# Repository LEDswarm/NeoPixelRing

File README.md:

# A custom NeoPixel ring for LEDswarm controllers

This repository contains the 3D model, schematic and PCB design of the circular NeoPixel boards designed for use with the LEDswarm controller enclosure. The design is inspired by NeoPixel Jewels, except this a special daughter board designed to mate with controller mainboards within [the 3D-printed enclosure](https://github.com/LEDswarm/enclosure).

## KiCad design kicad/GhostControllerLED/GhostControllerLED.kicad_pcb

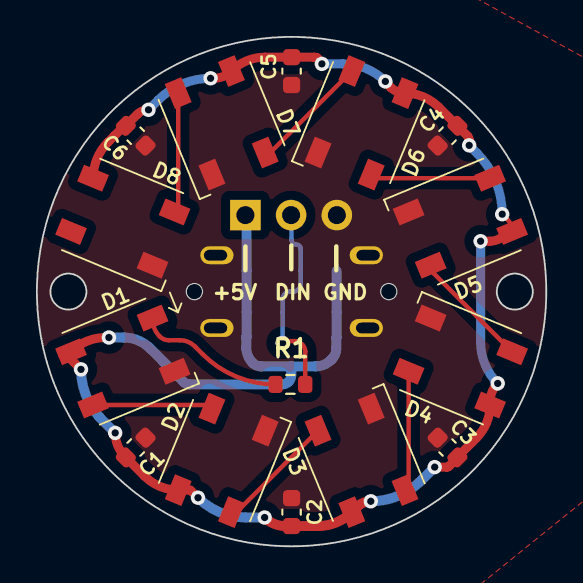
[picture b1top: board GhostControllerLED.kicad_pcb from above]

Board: 2 copper layers, 28.3 x 28.3 mm, 16 parts (1 on the bottom side), 11 nets.

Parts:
1: SK6812; LED_SK6812_PLCC4_5.0x5.0mm_P3.2mm
C1, C2, C3, C4, C5, C6: 100nF; C_0603_1608Metric
D2, D3, D4, D5, D6, D7, D8: SK6812; LED_SK6812_PLCC4_5.0x5.0mm_P3.2mm
NoUSB: Female LED Connector (No USB); Hanbo-Electronic-MC-118LS-H100 USB-C Socket
R1: 220; R_0603_1608Metric

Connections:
GND: 1.1 (VSS), C1.1, C2.1, C3.1, C4.1, C5.1, C6.1, D2.1 (VSS), D3.1 (VSS), D4.1 (VSS), D5.1 (VSS), D6.1 (VSS), D7.1 (VSS), D8.1 (VSS), NoUSB.1, NoUSB.2, NoUSB.3, NoUSB.A1 (GND), NoUSB.A12 (GND), NoUSB.B1 (GND), NoUSB.B12 (GND)
unnamed: 1.2 (DIN), R1.1
unnamed: 1.4 (DOUT), D2.2 (DIN)
unnamed: 1.3 (VDD), C1.2, C2.2, C3.2, C4.2, C5.2, C6.2, D2.3 (VDD), D3.3 (VDD), D4.3 (VDD), D5.3 (VDD), D6.3 (VDD), D7.3 (VDD), D8.3 (VDD), NoUSB.A4 (VBUS), NoUSB.A9 (VBUS), NoUSB.B4 (VBUS), NoUSB.B9 (VBUS)
unnamed: D2.4 (DOUT), D3.2 (DIN)
unnamed: D3.4 (DOUT), D4.2 (DIN)
unnamed: D4.4 (DOUT), D5.2 (DIN)
unnamed: D5.4 (DOUT), D6.2 (DIN)
unnamed: D6.4 (DOUT), D7.2 (DIN)
unnamed: D7.4 (DOUT), D8.2 (DIN), D8.4 (DOUT)
unnamed: NoUSB.A6 (D+), NoUSB.B6 (D+), R1.2

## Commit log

2024-03-17 feat: start working on a structured approach to 3d modeling the neopixel board
2024-03-17 feat: add programmatic distribution of leds around the tangential of a circle
2024-03-17 config: add PCB color and circle diameter for tangential LED placement
2024-03-17 chore: wrap led base into a module and mirror smd pins two by two
2024-03-17 chore: adjust led radius to have 0.6mm distance to the edge of the board from smd pad
2024-04-27 feat: push current state
2024-04-28 feat: add KiCad files
2024-04-28 chore: define gitignore
2024-04-28 chore: remove stupid macOS file
2024-04-28 doc: add image from KiCad
2024-04-29 chore: add copper fill zones
2024-04-29 feat: finalize LED board design to 1.0
2024-04-29 doc: add introductory paragraph
2024-04-29 feat: generate gerber files
2024-04-29 doc: update image banner

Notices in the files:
kicad/GhostControllerLED/GhostControllerLED.kicad_pcb:
© 2024 Moritz Riede
